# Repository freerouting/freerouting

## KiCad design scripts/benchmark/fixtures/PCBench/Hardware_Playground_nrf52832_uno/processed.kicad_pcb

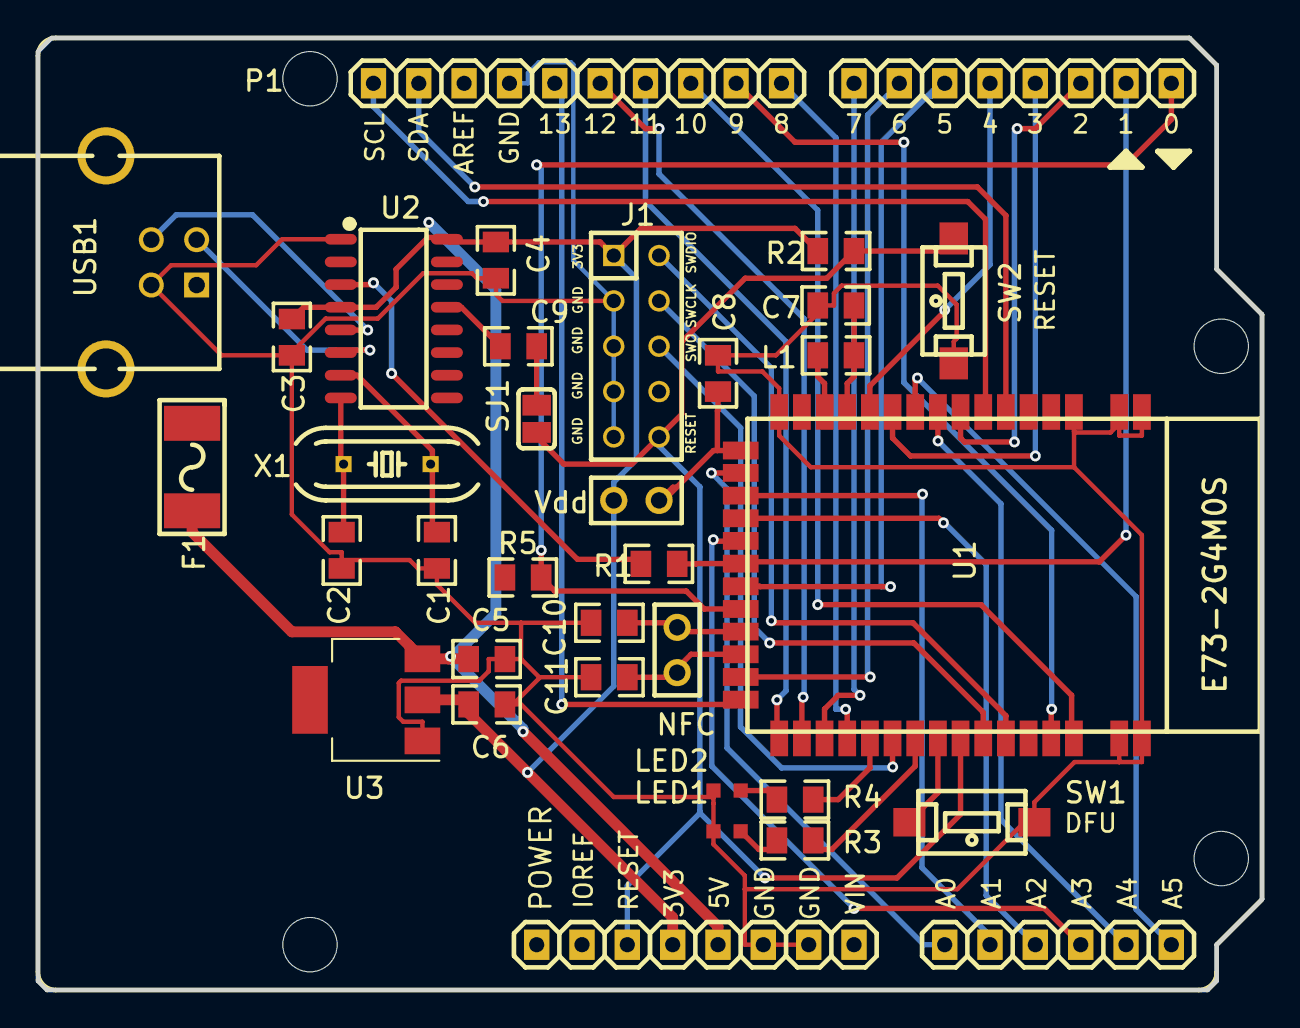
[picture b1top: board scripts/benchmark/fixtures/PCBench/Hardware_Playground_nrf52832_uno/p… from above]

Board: 2 copper layers, 68.6 x 53.3 mm, 36 parts (0 on the bottom side), 46 nets.

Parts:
C1, C2: 22p; 0805
C3, C9: 10n; 0805
C4: 100n; 0805
C5, C6: 22u; 0805
C7: 1u; 0805
C8: 10u; 0805
C10, C11: 300p; 0805
DESIGNED_WITH: LOGO_EASYEDA-TOP
F1: SMD Fuse; 1808F
J1: SWD; M2X5
L1: 10uH; 0805
LED1: BLUE; CHIPLED_0603
LED2: RED; CHIPLED_0603
NFC: NFC; 1X2
Noname_1, Noname_2, Noname_3: (no value)
P1: POWER; UNO_R3
R1, R3, R4, R5: 1K; 0805
R2: 10K; 0805
SJ1: DTR; SJ
SW1: DFU; SMD-6X3.6
SW2: RESET; SMD-6X3.6
U1: E73-2G4M0S; E73-2G4M04S
U2: CH340G; SOIC-16_150MIL
U3: AMS1117-3.3; SOT-223
USB1: USB-B-Female-TH_C46393; USB-M-49
Vdd: Vdd; 1X2
X1: 12MHz; HC-49S

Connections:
+3V3: C3.1, C4.2, C6.1, J1.1, P1.28, R2.2, U2.4, U2.16, U3.2, Vdd.1
+5V: C5.1, F1.2, P1.29, U3.3
A0: P1.19, U1.17
A1: P1.20, U1.18
A2: P1.21, U1.19
A3: P1.22, U1.20
A4: P1.23, U1.8
A5: P1.24, U1.9
C9_2: C9.2, SJ1.2
D2: P1.13, U1.7
D3: P1.14, U1.10
D4: P1.15, U1.11
D5: P1.16, U1.22
D6: P1.17, U1.26
D7: P1.18, U1.30
D8: P1.1, U1.31
D9: P1.2, U1.40
D10: P1.3, U1.41
D+: U2.5, USB1.3
D-: U2.6, USB1.2
DFU: SW1.2, U1.35
DTR: C9.1, U2.13
GND: C1.1, C2.1, C3.2, C4.1, C5.2, C6.2, C7.1, C8.1, C10.2, C11.2, J1.3, J1.5, J1.7, J1.9, LED1.C, LED2.C, P1.7, P1.30, P1.31, SW1.1, SW2.1, U1.0, U1.1, U1.2, U1.15, U1.42, U1.43, U2.1, U3.1, USB1.4
MISO: P1.5, U1.29
MOSI: P1.4, U1.28
R3_1: LED1.A, R3.1
R4_1: LED2.A, R4.1
RESET: J1.10, P1.27, R2.1, SJ1.1, SW2.2, U1.36
RXD: P1.11, R5.2, U1.23
SCK: P1.6, U1.27
SCL: P1.10, U1.6
SDA: P1.9, U1.5
SWCLK: J1.4, U1.37
SWDIO: J1.2, U1.38
SWO: J1.6, U1.33
TXD: P1.12, R1.2, U1.21
U1_12: C7.2, L1.1, U1.12
U1_13: L1.2, U1.13
U1_16: C8.2, U1.16, Vdd.2
U1_24: C10.1, NFC.1, U1.24
U1_25: C11.1, NFC.2, U1.25
U1_32: R4.2, U1.32
U1_34: R3.2, U1.34
U2_3: R1.1, U2.3
U2_7: C1.2, U2.7, X1.1
U2_8: C2.2, U2.8, X1.2

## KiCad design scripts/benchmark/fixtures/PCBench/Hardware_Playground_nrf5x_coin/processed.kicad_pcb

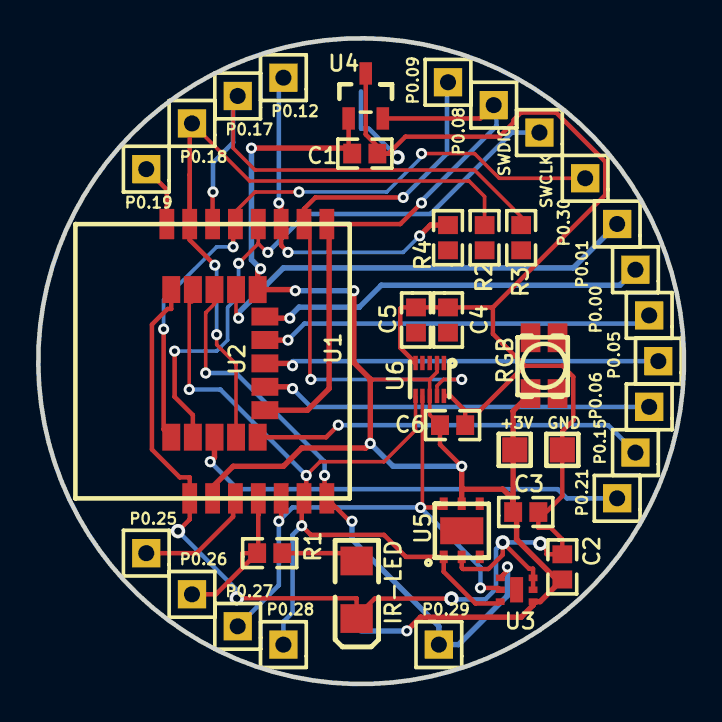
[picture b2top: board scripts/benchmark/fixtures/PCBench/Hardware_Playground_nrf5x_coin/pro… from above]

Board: 2 copper layers, 35.9 x 35.9 mm, 41 parts (0 on the bottom side), 23 nets.

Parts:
+3V: PAD-1.4X1.4-ALPS-H1.6
C1, C2, C3, C4, C5, C6: 100n; 0603
CR2032-3V: CR2032-BS-6-1; BATTERY-3
GND: PAD-1.4X1.4-ALPS-H1.6
IR-LED: IR LED; LED-1206
P0.00: P0.00; HDR-1X1_2.54
P0.01: P0.01; HDR-1X1_2.54
P0.05: P0.05; HDR-1X1_2.54
P0.06: P0.06; HDR-1X1_2.54
P0.08: P0.08; HDR-1X1_2.54
P0.09: P0.09; HDR-1X1_2.54
P0.12: P0.12; HDR-1X1_2.54
P0.15: P0.15; HDR-1X1_2.54
P0.17: P0.17; HDR-1X1_2.54
P0.18: P0.18; HDR-1X1_2.54
P0.19: P0.19; HDR-1X1_2.54
P0.21: P0.21; HDR-1X1_2.54
P0.25: P0.25; HDR-1X1_2.54
P0.26: P0.26; HDR-1X1_2.54
P0.27: P0.27; HDR-1X1_2.54
P0.28: P0.28; HDR-1X1_2.54
P0.29: P0.29; HDR-1X1_2.54
P0.30: P0.30; HDR-1X1_2.54
R1, R2, R3, R4: 100Ω; 0603
RGB: ASMB-MTB1-0A3A2; ASMB-MTB1-0A3A2-RGB-LED
SWCLK: SWCLK; HDR-1X1_2.54
SWDIO: SWDIO; HDR-1X1_2.54
U1: PTR5518
U2: ANT; HOLYIOT NRF52832
U3: MAX44009EDT+; MAXM-D622N+4_V
U4: DRV5032AJDBZR; SOT-23(SOT-23-3)
U5: HTU21D; DFN-6-EP
U6: MAG3110FCR1; DFN-10

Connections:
+3V: +3V.1, C1.2, C2.2, C3.1, C6.1, CR2032-3V.1, RGB.1, U1.P$10, U2.11, U3.1, U4.1, U5.5, U6.2, U6.8
GND: C1.1, C2.1, C3.2, C4.1, C5.1, C6.2, CR2032-3V.2, GND.1, IR-LED.2, U1.P$9, U2.15, U3.2, U3.3, U4.3, U5.2, U6.5, U6.10
LED1_1: IR-LED.1, R1.2
P0.00: P0.00.1, U2.9
P0.01: P0.01.1, U2.10
P0.05: P0.05.1, U2.8
P0.06: P0.06.1, U2.7
P0.08: P0.08.1, U1.P$1, U2.6, U4.2
P0.09: P0.09.1, U1.P$2, U6.9
P0.12: P0.12.1, R4.2, U1.P$3
P0.15: P0.15.1, U2.5
P0.17: P0.17.1, R3.2, U1.P$6
P0.18: P0.18.1, R2.2, U1.P$7, U2.4
P0.19: P0.19.1, U1.P$8
P0.21: P0.21.1, U2.3
P0.25: P0.25.1, U1.P$11
P0.26: P0.26.1, R1.1, U1.P$12
P0.27: P0.27.1, U1.P$13, U3.5, U5.6, U6.7
P0.28: P0.28.1, U1.P$14, U2.14, U3.6, U5.1, U6.6
P0.29: P0.29.1, U1.P$15, U2.13, U3.4
P0.30: P0.30.1, U2.12
SWCLK: SWCLK.1, U1.P$5, U2.1
SWDIO: SWDIO.1, U1.P$4, U2.2

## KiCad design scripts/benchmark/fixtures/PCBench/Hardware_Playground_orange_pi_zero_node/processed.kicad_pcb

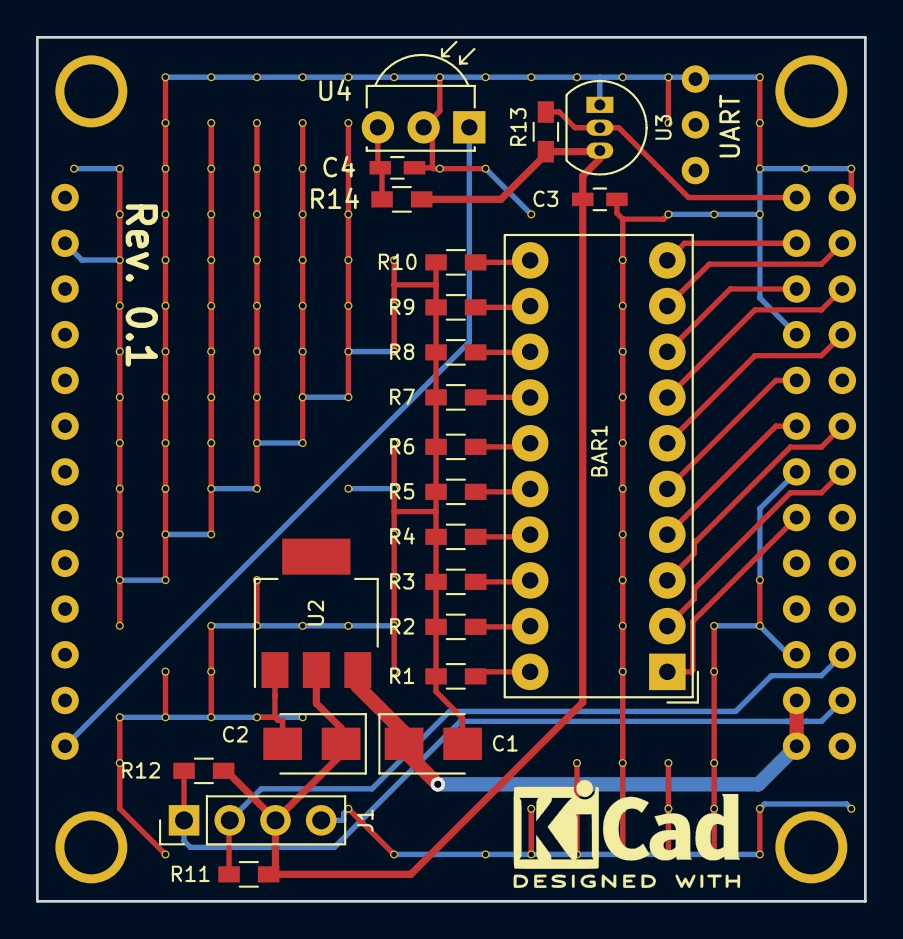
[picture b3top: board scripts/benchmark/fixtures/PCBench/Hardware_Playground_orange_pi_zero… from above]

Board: 2 copper layers, 46.0 x 48.0 mm, 163 parts (0 on the bottom side), 28 nets.

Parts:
BAR1: HDSP-4850_2; HDSP-4850
C1, C2: 22u; CP_Tantalum_Case-B_EIA-3528-21_Wave
C3, C4: 100n; C_0603_HandSoldering
J1: Conn_01x04; Pin_Header_Straight_1x04_Pitch2.54mm
R1, R2, R3, R4, R5, R6, R7, R8, R9, R10: 330; R_0603_HandSoldering
R11, R12, R13: 4K7; R_0603_HandSoldering
R14: 100; R_0603_HandSoldering
U1: orange_pi_zero; orangepi-zero
U2: AMS1117-3.3; SOT-223
U3: DS18B20; TO-92_Inline_Narrow_Oval
U4: TSOP343xx; IRReceiver_Vishay_MOLD-3pin
V1_3, V2_3, V2_4, V2_5, V2_6, V2_7, V2_8, V2_9, V2_10, V2_11, V2_12, V2_13, V2_15, V2_16, V3_1, V3_2, V3_3, V3_4, V3_5, V3_6, V3_7, V3_8, V3_9, V3_10, V3_11, V3_12, V3_14, V3_15, V3_18, V4_1, V4_2, V4_3, V4_4, V4_5, V4_6, V4_7, V4_8, V4_9, V4_10, V4_11, V4_13, V4_14, V4_15, V5_1, V5_2, V5_3, V5_4, V5_5, V5_6, V5_7, V5_8, V5_9, V5_10, V5_12, V5_13, V5_15, V6_1, V6_2, V6_3, V6_4, V6_5, V6_6, V6_7, V6_8, V6_9, V6_13, V6_15, V7_1, V7_2, V7_3, V7_4, V7_5, V7_6, V7_7, V7_8, V7_10, V7_13, V7_17, V8_1, V8_5, V8_6, V8_7, V8_9, V8_10, V8_11, V8_12, V8_13, V8_14, V8_18, V9_1, V9_3, V10_1, V10_3, V10_18, V11_1, V11_4, V11_17, V11_18, V12_1, V12_16, V12_17, V12_18, V13_1, V13_5, V13_6, V13_7, V13_8, V13_9, V13_10, V13_11, V13_12, V13_13, V13_14, V13_16, V13_17, V13_18, V14_1, V14_2, V14_4, V14_16, V14_17, V14_18, V15_4, V15_13, V15_14, V15_16, V15_17, V15_18, V16_1, V16_2, V16_3, V16_4, V16_12, V16_13, V16_17, V16_18, V17_3, V18_3, V18_17: AUTO_VIA; VIA_MATRIX

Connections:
+3V3: C2.1, C3.2, J1.3, R11.2, R12.2, R13.2, R14.2, U2.2, U3.3
+5V: C1.1, U1.102, U1.104, U2.3
GND: C1.2, C2.2, C3.1, C4.1, J1.4, R1.1, R2.1, R3.1, R4.1, R5.1, R6.1, R7.1, R8.1, R9.1, R10.1, U1.2, U1.106, U1.114, U1.120, U1.125, U1.201, U2.1, U3.1, U4.2, V1_3.1, V2_3.1, V2_4.1, V2_5.1, V2_6.1, V2_7.1, V2_8.1, V2_9.1, V2_10.1, V2_11.1, V2_12.1, V2_13.1, V2_15.1, V2_16.1, V3_1.1, V3_2.1, V3_3.1, V3_4.1, V3_5.1, V3_6.1, V3_7.1, V3_8.1, V3_9.1, V3_10.1, V3_11.1, V3_12.1, V3_14.1, V3_15.1, V3_18.1, V4_1.1, V4_2.1, V4_3.1, V4_4.1, V4_5.1, V4_6.1, V4_7.1, V4_8.1, V4_9.1, V4_10.1, V4_11.1, V4_13.1, V4_14.1, V4_15.1, V5_1.1, V5_2.1, V5_3.1, V5_4.1, V5_5.1, V5_6.1, V5_7.1, V5_8.1, V5_9.1, V5_10.1, V5_12.1, V5_13.1, V5_15.1, V6_1.1, V6_2.1, V6_3.1, V6_4.1, V6_5.1, V6_6.1, V6_7.1, V6_8.1, V6_9.1, V6_13.1, V6_15.1, V7_1.1, V7_2.1, V7_3.1, V7_4.1, V7_5.1, V7_6.1, V7_7.1, V7_8.1, V7_10.1, V7_13.1, V7_17.1, V8_1.1, V8_5.1, V8_6.1, V8_7.1, V8_9.1, V8_10.1, V8_11.1, V8_12.1, V8_13.1, V8_14.1, V8_18.1, V9_1.1, V9_3.1, V10_1.1, V10_3.1, V10_18.1, V11_1.1, V11_4.1, V11_17.1, V11_18.1, V12_1.1, V12_16.1, V12_17.1, V12_18.1, V13_1.1, V13_5.1, V13_6.1, V13_7.1, V13_8.1, V13_9.1, V13_10.1, V13_11.1, V13_12.1, V13_13.1, V13_14.1, V13_16.1, V13_17.1, V13_18.1, V14_1.1, V14_2.1, V14_4.1, V14_16.1, V14_17.1, V14_18.1, V15_4.1, V15_13.1, V15_14.1, V15_16.1, V15_17.1, V15_18.1, V16_1.1, V16_2.1, V16_3.1, V16_4.1, V16_12.1, V16_13.1, V16_17.1, V16_18.1, V17_3.1, V18_3.1, V18_17.1
unnamed: BAR1.1, U1.112
unnamed: BAR1.2, U1.113
unnamed: BAR1.3, U1.115
unnamed: BAR1.4, U1.116
unnamed: BAR1.5, U1.118
unnamed: BAR1.6, U1.119
unnamed: BAR1.7, U1.121
unnamed: BAR1.8, U1.122
unnamed: BAR1.9, U1.123
unnamed: BAR1.10, U1.124
unnamed: BAR1.11, R10.2
unnamed: BAR1.12, R9.2
unnamed: BAR1.13, R8.2
unnamed: BAR1.14, R7.2
unnamed: BAR1.15, R6.2
unnamed: BAR1.16, R5.2
unnamed: BAR1.17, R4.2
unnamed: BAR1.18, R3.2
unnamed: BAR1.19, R2.2
unnamed: BAR1.20, R1.2
unnamed: C4.2, R14.1, U4.3
unnamed: J1.1, R12.1, U1.103
unnamed: J1.2, R11.1, U1.105
unnamed: R13.1, U1.126, U3.2
unnamed: U1.13, U4.1
